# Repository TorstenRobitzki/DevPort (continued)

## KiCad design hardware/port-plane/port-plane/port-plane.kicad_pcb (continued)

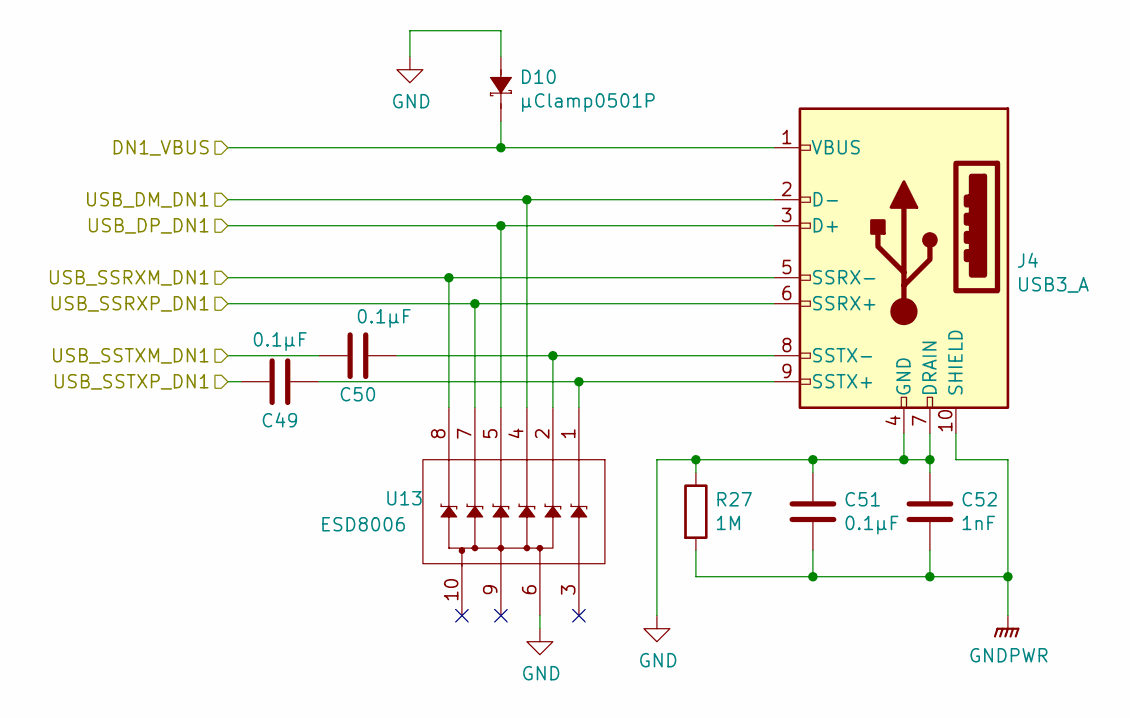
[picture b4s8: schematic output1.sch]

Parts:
C49, C50: 0.1µF; C_0201_0603Metric
C51: 0.1µF; C_0603_1608Metric
C52: 1nF; C_0603_1608Metric
D10: µClamp0501P; SLP1006P2
J4: USB3_A; WR-COM_USB_3.0_Horizontal_SMT
R27: 1M; R_0603_1608Metric
U13: ESD8006; UDFN8

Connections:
/hub/USB_DM_DN1: J4.2 (D-), U13.4; also elsewhere on the board
/hub/USB_DP_DN1: J4.3 (D+), U13.5; also elsewhere on the board
/hub/USB_SSRXM_DN1: J4.5 (SSRX-), U13.8; also elsewhere on the board
/hub/USB_SSRXP_DN1: J4.6 (SSRX+), U13.7; also elsewhere on the board
/hub/USB_SSTXM_DN1: C50.2; also elsewhere on the board
/hub/USB_SSTXP_DN1: C49.2; also elsewhere on the board
/outputs/DN1_VBUS: D10.2 (K), J4.1 (VBUS); also elsewhere on the board
GND: C51.1, C52.1, D10.1 (A), J4.4 (GND), J4.7 (DRAIN), R27.1, U13.6; also elsewhere on the board
GNDPWR: C51.2, C52.2, J4.10 (SHIELD), R27.2; also elsewhere on the board
unnamed: C49.1, J4.9 (SSTX+), U13.1
unnamed: C50.1, J4.8 (SSTX-), U13.2

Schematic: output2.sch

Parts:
C53, C54: 0.1µF; C_0201_0603Metric
C55: 0.1µF; C_0603_1608Metric
C56: 1nF; C_0603_1608Metric
D11: µClamp0501P; SLP1006P2
J5: USB3_A; WR-COM_USB_3.0_Horizontal_SMT
R28: 1M; R_0603_1608Metric
U14: ESD8006; UDFN8

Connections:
/hub/USB_DM_DN2: J5.2 (D-), U14.4; also elsewhere on the board
/hub/USB_DP_DN2: J5.3 (D+), U14.5; also elsewhere on the board
/hub/USB_SSRXM_DN2: J5.5 (SSRX-), U14.8; also elsewhere on the board
/hub/USB_SSRXP_DN2: J5.6 (SSRX+), U14.7; also elsewhere on the board
/hub/USB_SSTXM_DN2: C54.2; also elsewhere on the board
/hub/USB_SSTXP_DN2: C53.2; also elsewhere on the board
/outputs/DN2_VBUS: D11.2 (K), J5.1 (VBUS); also elsewhere on the board
GND: C55.1, C56.1, D11.1 (A), J5.4 (GND), J5.7 (DRAIN), R28.1, U14.6; also elsewhere on the board
GNDPWR: C55.2, C56.2, J5.10 (SHIELD), R28.2; also elsewhere on the board
unnamed: C53.1, J5.9 (SSTX+), U14.1
unnamed: C54.1, J5.8 (SSTX-), U14.2

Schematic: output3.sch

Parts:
C57, C58: 0.1µF; C_0201_0603Metric
C59: 0.1µF; C_0603_1608Metric
C60: 1nF; C_0603_1608Metric
D12: µClamp0501P; SLP1006P2
J6: USB3_A; WR-COM_USB_3.0_Horizontal_SMT
R29: 1M; R_0603_1608Metric
U15: ESD8006; UDFN8

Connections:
/hub/USB_DM_DN3: J6.2 (D-), U15.4; also elsewhere on the board
/hub/USB_DP_DN3: J6.3 (D+), U15.5; also elsewhere on the board
/hub/USB_SSRXM_DN3: J6.5 (SSRX-), U15.8; also elsewhere on the board
/hub/USB_SSRXP_DN3: J6.6 (SSRX+), U15.7; also elsewhere on the board
/hub/USB_SSTXM_DN3: C58.2; also elsewhere on the board
/hub/USB_SSTXP_DN3: C57.2; also elsewhere on the board
/outputs/DN3_VBUS: D12.2 (K), J6.1 (VBUS); also elsewhere on the board
GND: C59.1, C60.1, D12.1 (A), J6.4 (GND), J6.7 (DRAIN), R29.1, U15.6; also elsewhere on the board
GNDPWR: C59.2, C60.2, J6.10 (SHIELD), R29.2; also elsewhere on the board
unnamed: C57.1, J6.9 (SSTX+), U15.1
unnamed: C58.1, J6.8 (SSTX-), U15.2

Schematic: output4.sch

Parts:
C61, C62: 0.1µF; C_0201_0603Metric
C63: 0.1µF; C_0603_1608Metric
C64: 1nF; C_0603_1608Metric
D13: µClamp0501P; SLP1006P2
J7: USB3_A; WR-COM_USB_3.0_Horizontal_SMT
R30: 1M; R_0603_1608Metric
U16: ESD8006; UDFN8

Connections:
/hub/USB_DM_DN4: J7.2 (D-), U16.4; also elsewhere on the board
/hub/USB_DP_DN4: J7.3 (D+), U16.5; also elsewhere on the board
/hub/USB_SSRXM_DN4: J7.5 (SSRX-), U16.8; also elsewhere on the board
/hub/USB_SSRXP_DN4: J7.6 (SSRX+), U16.7; also elsewhere on the board
/hub/USB_SSTXM_DN4: C62.2; also elsewhere on the board
/hub/USB_SSTXP_DN4: C61.2; also elsewhere on the board
/outputs/DN4_VBUS: D13.2 (K), J7.1 (VBUS); also elsewhere on the board
GND: C63.1, C64.1, D13.1 (A), J7.4 (GND), J7.7 (DRAIN), R30.1, U16.6; also elsewhere on the board
GNDPWR: C63.2, C64.2, J7.10 (SHIELD), R30.2; also elsewhere on the board
unnamed: C61.1, J7.9 (SSTX+), U16.1
unnamed: C62.1, J7.8 (SSTX-), U16.2

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
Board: 2 copper layers, 153 parts (4 on the bottom side), 115 nets, no tracks yet.

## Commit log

2021-03-10 initial firmware commit
2021-03-11 reading writing i2c
2021-03-17 progress....
2021-03-17 add hardware
2021-04-08 silkscreen R13; C27 vertauscht
2021-06-14 move to target hardware without bootloader; 12Mhz external Osc.; LED test
2021-06-16 set GCLK_MAIN to 120 MHz
2021-06-16 reading the temperature sensor
2021-06-17 kleinere Anpassungen
2021-06-17 HUB works aswell
2021-06-25 USB CDC sketch
2021-06-30 USB CDC
2021-07-01 delay before sending welcome message
